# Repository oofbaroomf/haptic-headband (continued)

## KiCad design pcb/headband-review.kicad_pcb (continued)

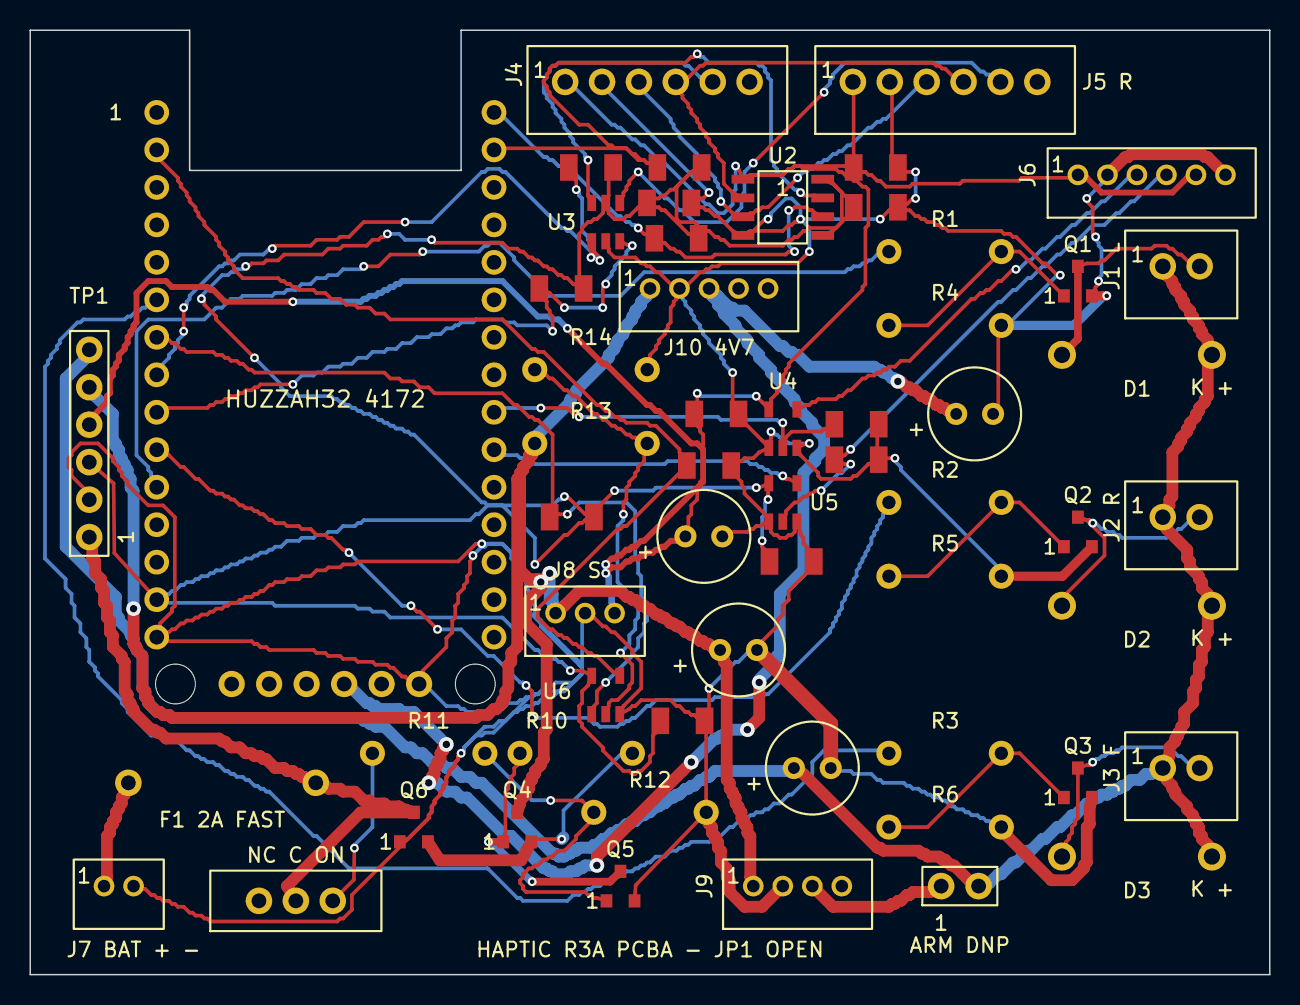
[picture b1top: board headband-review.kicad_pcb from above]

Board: 2 copper layers, 84.0 x 64.0 mm, 58 parts (0 on the bottom side), 37 nets.

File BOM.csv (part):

"Category","Reference","Quantity","Functional description","Manufacturer","Manufacturer part number","Supplier","Supplier part number","Component value","Package","Footprint","THT/SMD","Electrical rating","Verified datasheet link","Verification status","Assembly notes","Procurement status","Supplier link"
"Prebuilt module on carrier","U1","1","Exact purchased controller","Adafruit","4172","To source","","","HUZZAH32 breakout","CAD-derived 36 pads","Socketed THT","VIN34 receives regulated4.70V; BAT30 NC","https://github.com/adafruit/Adafruit-ESP32-HUZZAH-Breakout-PCB","CAD verified; physical fit pending","Two 15-way socket rows plus insulated VIN34 service jumper; leave programming interface accessible; use signal-only programming cable, VIN power contact isolated","Purchased (user reported)","https://github.com/adafruit/Adafruit-ESP32-HUZZAH-Breakout-PCB"
"Controller PCB","Q1 Q2 Q3 Q5","4","Three motor switches and power-gate control","Diodes Incorporated","DMN2056U-7","JLCPCB assembly","C332302","","SOT23","Sot23 G1 S2 D3","SMD","20V; RDSon <=85mohm at VGS1.5V at25C","https://www.diodes.com/datasheet/download/DMN2056U.pdf","Datasheet/land pattern verified","New selection; not purchased PN2222; qualify thermal layout","Included in R3A PCBA; not yet ordered","https://jlcpcb.com/partdetail/C332302"
"Controller PCB","Q4 Q6","2","High-side power and reverse battery protection","Diodes Incorporated","DMP2035U-7","JLCPCB assembly","C110499","","SOT23","Sot23 G1 S2 D3","SMD","-20V; RDSon <=45mohm at VGS-2.5V at25C","https://www.diodes.com/datasheet/download/DMP2035U.pdf","Datasheet/land pattern verified","Q6 D to raw battery; Q4 S to protected battery","Included in R3A PCBA; not yet ordered","https://jlcpcb.com/partdetail/C110499"
"Controller PCB","D1 D2 D3","3","Motor flyback rectifiers","STMicroelectronics","1N5819","JLCPCB assembly","C110032","","DO-41","Axial P10.16 D2.7 L5.2","THT","40V 1A; transient energy still unqualified","https://www.st.com/resource/en/datasheet/1n5819.pdf","Published rating verified; bench clamp test pending","Cathode band goes to motor positive/pad2","Included in R3A PCBA; not yet ordered","https://jlcpcb.com/partdetail/C110032"
"Controller PCB","R1 R2 R3","3","Gate resistors","Yageo","MFR-25FTF52-330R","JLCPCB assembly","C1372966","330 ohm","0.25W axial","Axial DIN0207 P7.62 D2.5 L6.3","THT","0.25W 1%; body6.3x2.4mm","https://www.yageogroup.com/component-documentation/download/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","Family/ordering code verified; purchased stock fit pending","Selected new orderable part; compare existing purchased resistors before reuse","Included in R3A PCBA; not yet ordered","https://jlcpcb.com/partdetail/C1372966"
"Controller PCB","R4 R5 R6","3","Strong reset-state motor OFF bias","Yageo","MFR-25FBF52-1K","JLCPCB assembly","C1364484","1k ohm","0.25W axial","Axial DIN0207 P7.62 D2.5 L6.3","THT","0.25W 1%; body6.3x2.4mm","https://www.yageogroup.com/component-documentation/download/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","Family/ordering code verified; purchased stock fit pending","Selected new orderable part; compare existing purchased resistors before reuse","Included in R3A PCBA; not yet ordered","https://jlcpcb.com/partdetail/C1364484"
"Controller PCB","R12","1","Power-gate enable pulldown","Yageo","MFR-25FTE52-100K","JLCPCB assembly","C172965","100k ohm","0.25W axial","Axial DIN0207 P7.62 D2.5 L6.3","THT","0.25W 1%; body6.3x2.4mm","https://www.yageogroup.com/component-documentation/download/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","Family/ordering code verified; purchased stock fit pending","Selected new orderable part; compare existing purchased resistors before reuse","Included in R3A PCBA; not yet ordered","https://jlcpcb.com/partdetail/C172965"
"Controller PCB","R10 R11 R13 R14","4","Power gate pullup and switch series resistor","Yageo","MFR-25FTE52-10K","JLCPCB assembly","C172967","10k ohm","0.25W axial","Axial DIN0207 P7.62 D2.5 L6.3","THT","0.25W 1%; body6.3x2.4mm","https://www.yageogroup.com/component-documentation/download/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","Family/ordering code verified; purchased stock fit pending","Selected new orderable part; compare existing purchased resistors before reuse","Included in R3A PCBA; not yet ordered","https://jlcpcb.com/partdetail/C172967"
"Controller PCB","C1","1","Bulk/sensor decoupling","Panasonic","EEUFR1A221","JLCPCB assembly","C407869","220uF","Radial electrolytic","Radial D6.3 P2.5","THT","10V;455mArms100kHz;.13ohm","https://industrial.panasonic.com/content/data/CP/PDF/S_Alm_A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","Manufacturer dimensions verified; operating ripple test pending","Positive lead pad1; C1/C2 height11.2mm; C3 height11.0mm","Included in R3A PCBA; not yet ordered","https://jlcpcb.com/partdetail/C407869"
"Controller PCB","C2","1","Bulk/sensor decoupling","Panasonic","EEUFM1E101","JLCPCB assembly","C713389","100uF","Radial electrolytic","Radial D6.3 P2.5","THT","25V;455mArms100kHz;0.13ohm;2000h105C","https://industrial.panasonic.com/content/data/CP/PDF/S_Alm_A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","Manufacturer dimensions verified; operating ripple test pending","Positive lead pad1; C1/C2 height11.2mm; C3 height11.0mm","Included in R3A PCBA; not yet ordered","https://jlcpcb.com/partdetail/C713389"
"Controller PCB","C3","1","Bulk/sensor decoupling","Panasonic","EEUFM1E101","JLCPCB assembly","C713389","100uF","Radial electrolytic","Radial D6.3 P2.5","THT","25V;455mArms100kHz;0.13ohm;2000h105C","https://industrial.panasonic.com/content/data/CP/PDF/S_Alm_A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","Manufacturer dimensions verified; operating ripple test pending","Positive pad1. Replaces 47uF; sensor reservoir only. New R3A footprint.","Included in R3A PCBA; not yet ordered","https://jlcpcb.com/partdetail/C713389"
"Controller PCB","C10","1","Controller-input radio-burst reservoir","Panasonic","EEUFR1A221","JLCPCB assembly","C407869","220uF","Radial electrolytic","Radial D6.3 P2.5","THT","10V; 455mArms at100kHz; ESR0.13ohm","https://industrial.panasonic.com/content/data/CP/PDF/S_Alm_A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","Manufacturer footprint checked; transient qualification required","Positive pad1 to VCTRL_4V7; leave room for 11.2mm height","Included in R3A PCBA; not yet ordered","https://jlcpcb.com/partdetail/C407869"
"Controller PCB","SW1","1","Purchased physical slide switch","Adafruit / Dongguan Haoyu","805 / SS-12E17G2","To source","","","SPDT THT","Switch805 P2.50 drill1.0","THT","0.5A DC50V; carries enable current only","https://cdn-shop.adafruit.com/product-files/805/SS-12E17G2-r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","Drawing inspected; purchased fit pending","Common2; unused1 NC; ON3; continuity-test actuator direction","Purchased (user reported)","https://cdn-shop.adafruit.com/product-files/805/SS-12E17G2-r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"
"Controller PCB","J1 J2 J3","3","Motor interfaces","JST","B2B-XH-A(LF)(SN)","JLCPCB assembly","C158012","2 positions","XH keyed vertical header","XH 2x1 P2.5","THT","3A with specified contacts","https://www.jst.com/wp-content/uploads/2025/06/eXH.pdf","Manufacturer geometry checked; actual mating harness pending","Component-side pin1 at left; PH regulator unused positions NC; no unkeyed substitutes","Included in R3A PCBA; not yet ordered","https://jlcpcb.com/partdetail/C158012"
"Controller PCB","J4 J5","2","ToF interfaces","JST","B6B-XH-A(LF)(SN)","JLCPCB assembly","C144397","6 positions","XH keyed vertical header","XH 6x1 P2.5","THT","3A with specified contacts","https://www.jst.com/wp-content/uploads/2025/06/eXH.pdf","Manufacturer geometry checked; actual mating harness pending","Component-side pin1 at left; PH regulator unused positions NC; no unkeyed substitutes","Included in R3A PCBA; not yet ordered","https://jlcpcb.com/partdetail/C144397"
"Controller PCB","J6","1","IMU interface","JST","B6B-PH-K-S(LF)(SN)","JLCPCB assembly","C131342","6 positions","PH keyed vertical header","PH 6x1 P2","THT","2A with specified AWG24 contacts","https://www.jst.com/wp-content/uploads/2021/08/ePH-new.pdf","Manufacturer geometry checked; actual mating harness pending","Component-side pin1 at left; PH regulator unused positions NC; no unkeyed substitutes","Included in R3A PCBA; not yet ordered","https://jlcpcb.com/partdetail/C131342"
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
